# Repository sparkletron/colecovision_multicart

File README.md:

# Colecovision Multicart
## 15 in 1 flash ROM cart for Colecovision 32KiB ROMS.

author: Jay Convertino  

date: 2024.10.26

license: MIT

## Release Versions
### Current

  - pre-alpha

### Past

  - none
  
## Requirements

  - KiCad v7.X
  - xc8 v2.31 or greater
  - sdcc v4.0.0 or greater
  - make (build-essential)

  Tested on Ubuntu 22.04

## Brief Information

  Be sure to pull ALL submodules. The command for this is...

  ```console
  git submodule update --init --recursive
  ```

  This project creates a complete 15 in 1 multicart for the Colecovision. It will generate the needed ROM
  image, and firmware. Provides all the files needed for PCB creation, and the 3D printed case creation.

  No valid Colecovision ROMs are included in this project. Only valid ROM is the multicart application
  generated by RODAC. Game ROMs in RODAC are random data written in various bank sizes for testing only.

  Each folder in this root directory contains a part of the project, they are as follows.
  - docs, all documentation and detailed user manual.
  - schematic, Electrical schematic and gerbers from KiCAD.
  - src, all source files used to build the Multicart launcher and PIC support chip firmware.
  - models, STL files for printing out cart shell.

## Detailed Information

  For detailed usage information, please navigate to one of the following sources. They are the same, just in a different format.

  - [colecovision_multicart.pdf](docs/manual/colecovision_multicart.pdf)
  - [github wiki](https://github.com/sparkletron/colecovision_multicart/wiki)

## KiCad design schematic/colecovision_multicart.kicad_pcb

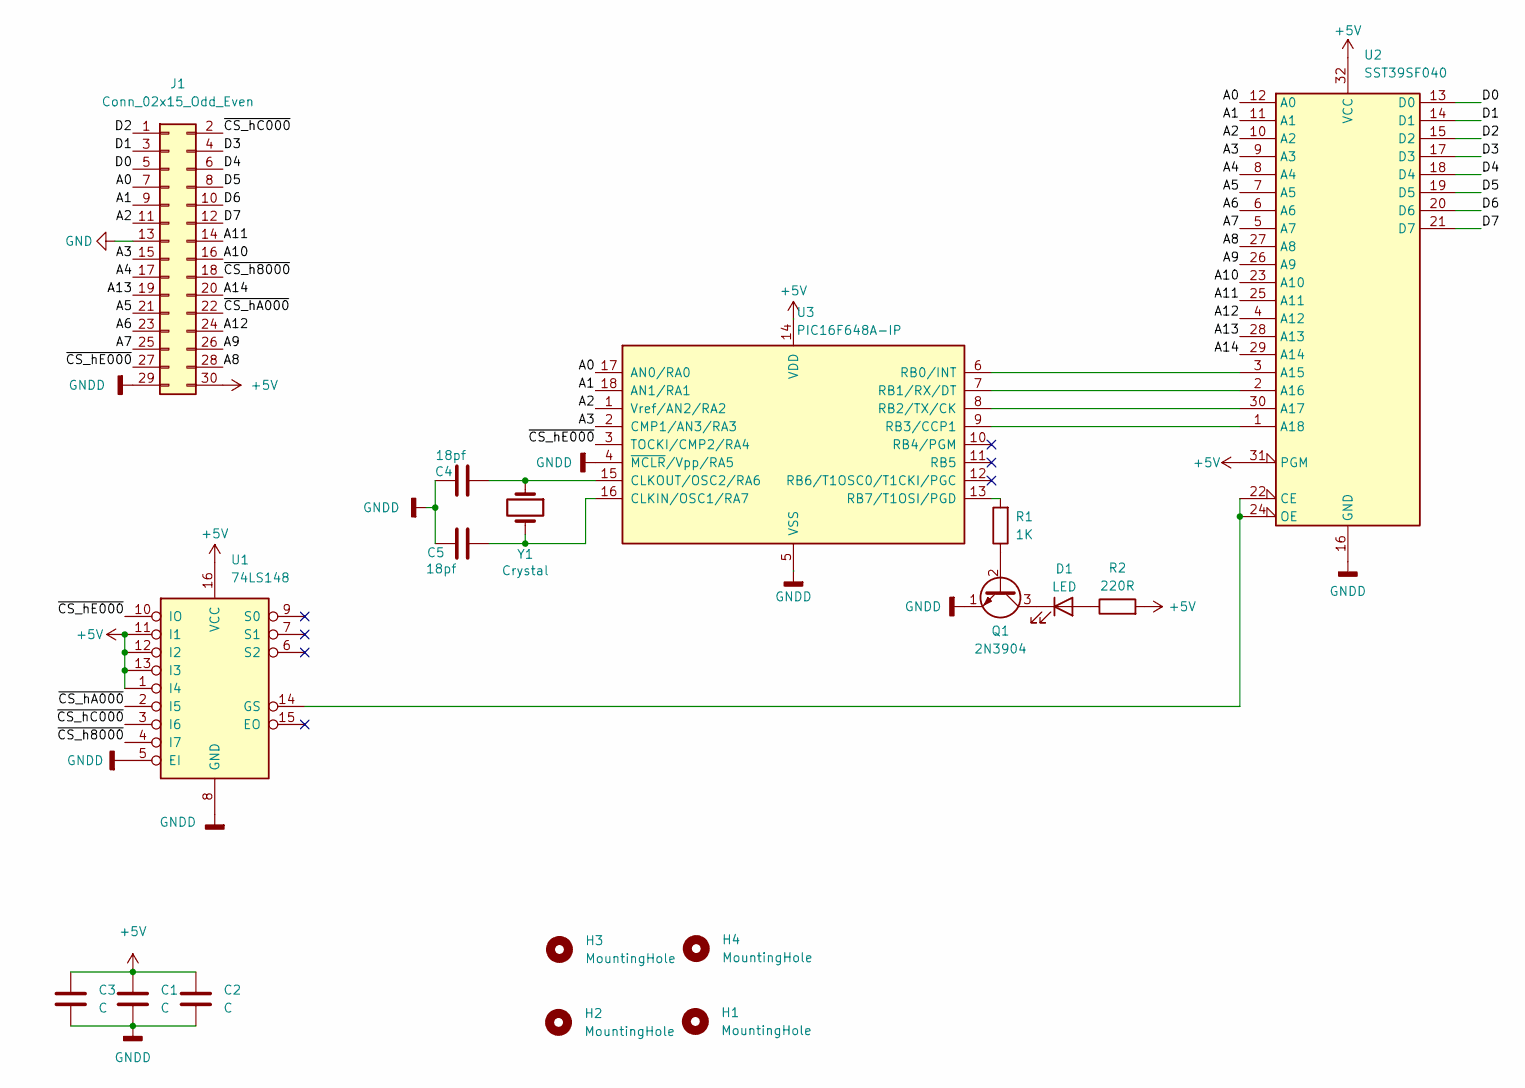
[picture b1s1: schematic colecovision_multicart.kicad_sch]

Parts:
C1, C2, C3: C; C_Disc_D5.0mm_W2.5mm_P5.00mm
C4, C5: 18pf; C_Disc_D3.0mm_W1.6mm_P2.50mm
D1: LED; LED_D3.0mm
H1, H2, H3, H4: MountingHole; MountingHole_3.2mm_M3_Pad
J1: Conn_02x15_Odd_Even; Colecovision_Cartridge
Q1: 2N3904; TO-92_Wide
R1: 1K; R_Axial_DIN0207_L6.3mm_D2.5mm_P7.62mm_Horizontal
R2: 220R; R_Axial_DIN0207_L6.3mm_D2.5mm_P7.62mm_Horizontal
U1: 74LS148; DIP-16_W7.62mm
U2: SST39SF040; DIP-32_W15.24mm
U3: PIC16F648A-IP; DIP-18_W7.62mm
Y1: Crystal; Crystal_HC49-4H_Vertical

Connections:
+5V: C1.1, C2.1, C3.1, J1.30, R2.2, U1.1 (I4), U1.11 (I1), U1.12 (I2), U1.13 (I3), U1.16 (VCC), U2.31 (PGM), U2.32 (VCC), U3.14 (VDD)
/A0: J1.7, U2.12 (A0), U3.17 (AN0/RA0)
/A1: J1.9, U2.11 (A1), U3.18 (AN1/RA1)
/A2: J1.11, U2.10 (A2), U3.1 (Vref/AN2/RA2)
/A3: J1.15, U2.9 (A3), U3.2 (CMP1/AN3/RA3)
/A4: J1.17, U2.8 (A4)
/A5: J1.21, U2.7 (A5)
/A6: J1.23, U2.6 (A6)
/A7: J1.25, U2.5 (A7)
/A8: J1.28, U2.27 (A8)
/A9: J1.26, U2.26 (A9)
/A10: J1.16, U2.23 (A10)
/A11: J1.14, U2.25 (A11)
/A12: J1.24, U2.4 (A12)
/A13: J1.19, U2.28 (A13)
/A14: J1.20, U2.29 (A14)
/D0: J1.5, U2.13 (D0)
/D1: J1.3, U2.14 (D1)
/D2: J1.1, U2.15 (D2)
/D3: J1.4, U2.17 (D3)
/D4: J1.6, U2.18 (D4)
/D5: J1.8, U2.19 (D5)
/D6: J1.10, U2.20 (D6)
/D7: J1.12, U2.21 (D7)
/~CS_h8000: J1.18, U1.4 (I7)
/~CS_hA000: J1.22, U1.2 (I5)
/~CS_hC000: J1.2, U1.3 (I6)
/~CS_hE000: J1.27, U1.10 (IO), U3.3 (TOCKI/CMP2/RA4)
GND: J1.13
GNDD: C1.2, C2.2, C3.2, C4.1, C5.2, J1.29, Q1.1 (E), U1.5 (EI), U1.8 (GND), U2.16 (GND), U3.4 (~MCLR/Vpp/RA5), U3.5 (VSS)
unnamed: D1.2 (A), R2.1
unnamed: D1.1 (K), Q1.3 (C)
unnamed: Q1.2 (B), R1.1
unnamed: U1.14 (GS), U2.22 (CE), U2.24 (OE)
unnamed: U2.3 (A15), U3.6 (RB0/INT)
unnamed: U2.2 (A16), U3.7 (RB1/RX/DT)
unnamed: U2.30 (A17), U3.8 (RB2/TX/CK)
unnamed: U2.1 (A18), U3.9 (RB3/CCP1)
unnamed: C5.1, U3.16 (CLKIN/OSC1/RA7), Y1.2
unnamed: C4.2, U3.15 (CLKOUT/OSC2/RA6), Y1.1
unnamed: R1.2, U3.13 (RB7/T1OSI/PGD)

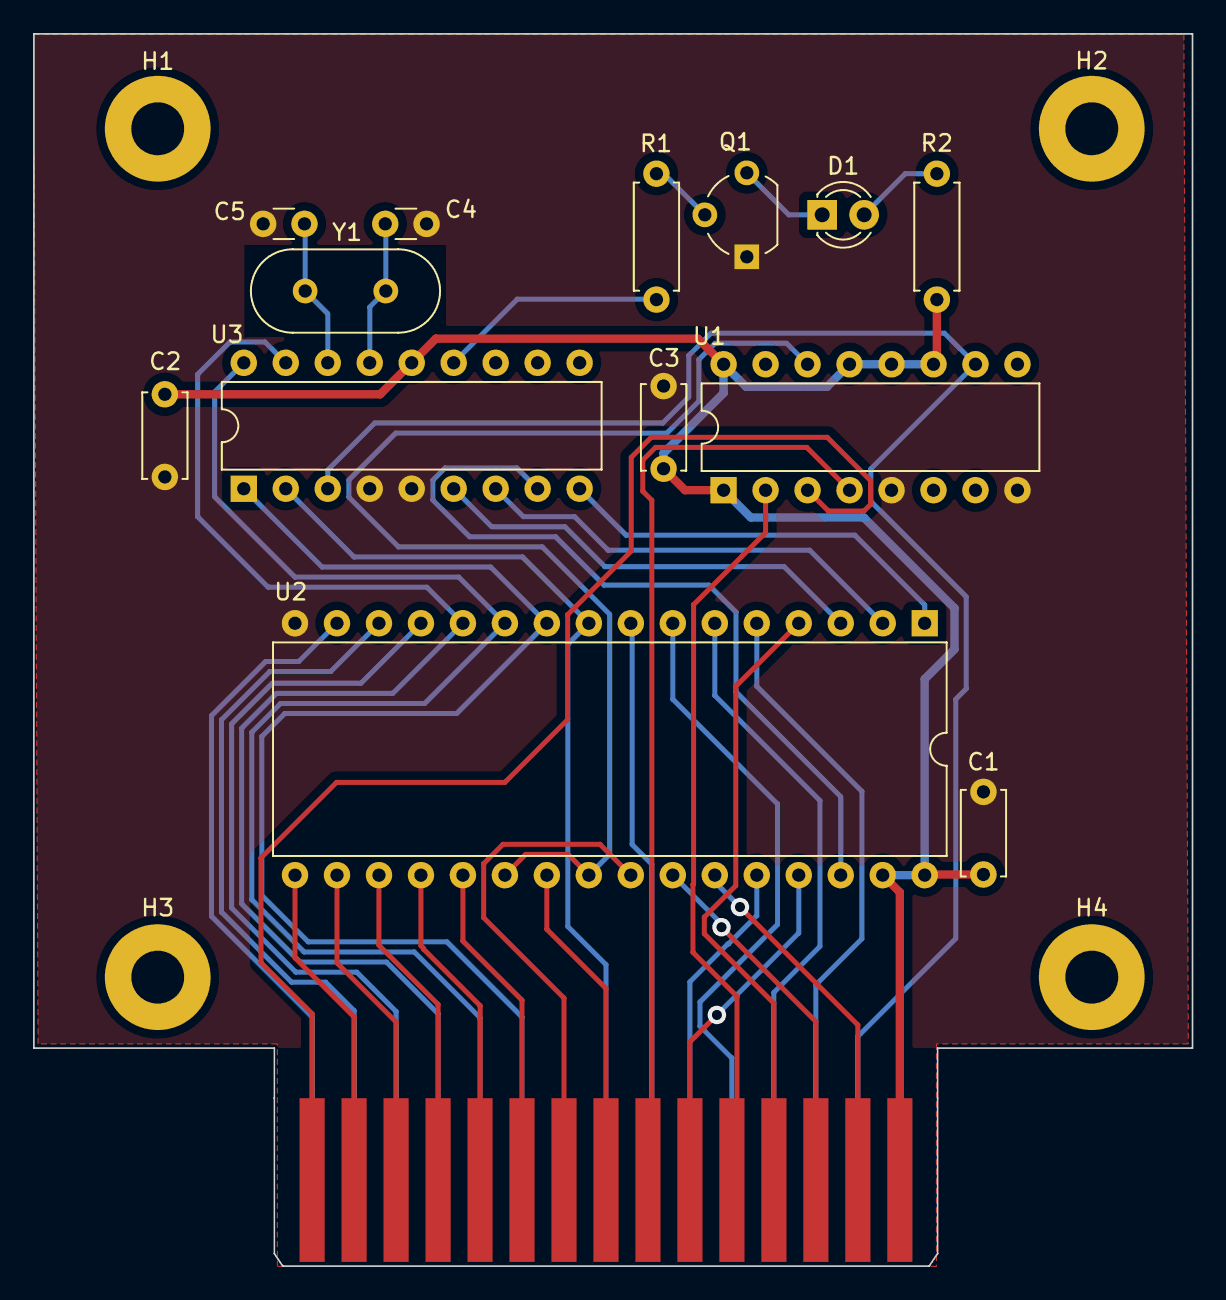
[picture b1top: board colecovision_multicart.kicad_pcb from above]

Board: 2 copper layers, 70.1 x 74.6 mm, 18 parts (0 on the bottom side), 40 nets.

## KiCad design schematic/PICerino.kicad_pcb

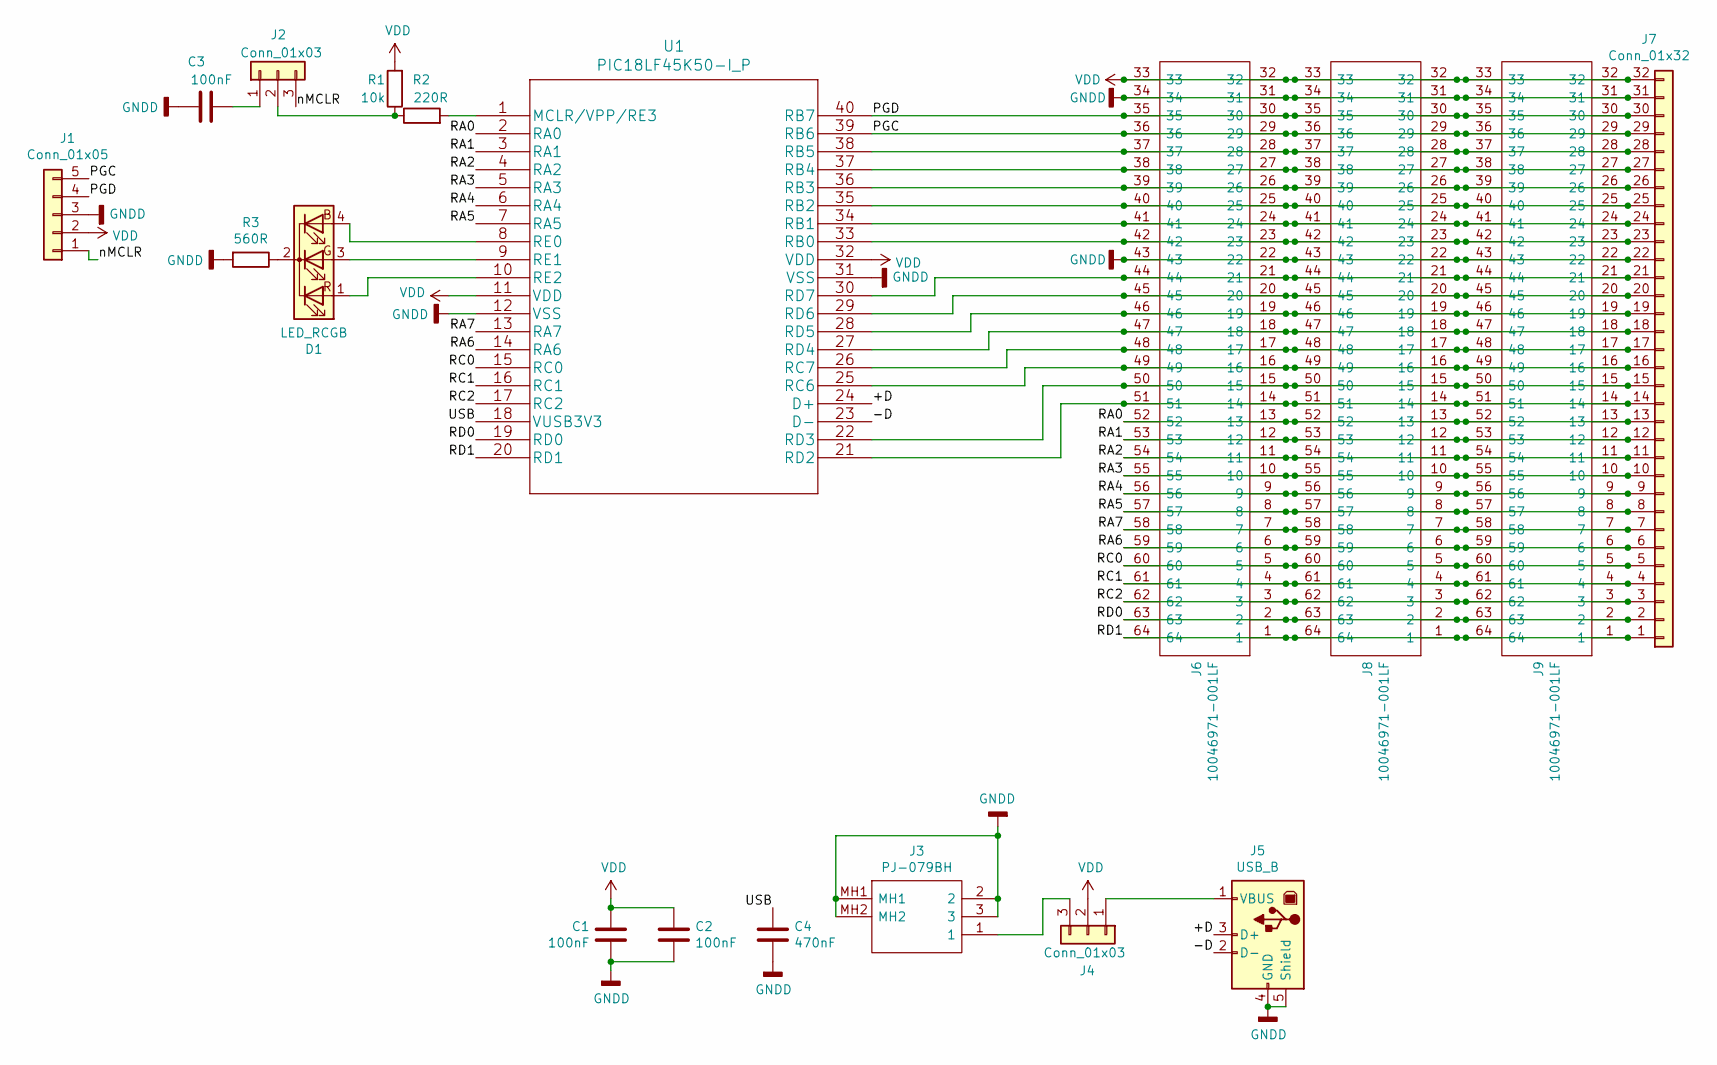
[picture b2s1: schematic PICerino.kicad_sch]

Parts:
C1, C2, C3: 100nF; C_Disc_D5.0mm_W2.5mm_P5.00mm
C4: 470nF; C_Disc_D5.0mm_W2.5mm_P5.00mm
D1: LED_RCGB; LED_D5.0mm-4_RGB_Wide_Pins
J1: Conn_01x05; PinHeader_1x05_P2.54mm_Vertical
J2, J4: Conn_01x03; PinHeader_1x03_P2.54mm_Vertical
J3: PJ-079BH; PJ079BH; Manufacturer_Part_Number PJ-079BH; Mouser Part Number 490-PJ-079BH
J5: USB_B; USB_B_OST_USB-B1HSxx_Horizontal
J6, J8, J9: 10046971-001LF; RHDR64W90P508X254_2X32_8786X929X1549P; Manufacturer_Part_Number 10046971-001LF; Mouser Part Number 649-10046971-001LF
J7: Conn_01x32; PinHeader_1x32_P2.54mm_Vertical
R1: 10k; R_Axial_DIN0207_L6.3mm_D2.5mm_P7.62mm_Horizontal
R2: 220R; R_Axial_DIN0207_L6.3mm_D2.5mm_P7.62mm_Horizontal
R3: 560R; R_Axial_DIN0207_L6.3mm_D2.5mm_P7.62mm_Horizontal
U1: PIC18LF45K50-I_P; DIP-40_W15.24mm_LongPads

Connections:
/+D: J5.3 (D+), U1.24 (D+)
/-D: J5.2 (D-), U1.23 (D-)
/PGC: J1.5, J6.29, J6.36, J7.29, J8.29, J8.36, J9.29, J9.36, U1.39 (RB6)
/PGD: J1.4, J6.30, J6.35, J7.30, J8.30, J8.35, J9.30, J9.35, U1.40 (RB7)
/RA0: J6.13, J6.52, J7.13, J8.13, J8.52, J9.13, J9.52, U1.2 (RA0)
/RA1: J6.12, J6.53, J7.12, J8.12, J8.53, J9.12, J9.53, U1.3 (RA1)
/RA2: J6.11, J6.54, J7.11, J8.11, J8.54, J9.11, J9.54, U1.4 (RA2)
/RA3: J6.10, J6.55, J7.10, J8.10, J8.55, J9.10, J9.55, U1.5 (RA3)
/RA4: J6.9, J6.56, J7.9, J8.9, J8.56, J9.9, J9.56, U1.6 (RA4)
/RA5: J6.8, J6.57, J7.8, J8.8, J8.57, J9.8, J9.57, U1.7 (RA5)
/RA6: J6.6, J6.59, J7.6, J8.6, J8.59, J9.6, J9.59, U1.14 (RA6)
/RA7: J6.7, J6.58, J7.7, J8.7, J8.58, J9.7, J9.58, U1.13 (RA7)
/RC0: J6.5, J6.60, J7.5, J8.5, J8.60, J9.5, J9.60, U1.15 (RC0)
/RC1: J6.4, J6.61, J7.4, J8.4, J8.61, J9.4, J9.61, U1.16 (RC1)
/RC2: J6.3, J6.62, J7.3, J8.3, J8.62, J9.3, J9.62, U1.17 (RC2)
/RD0: J6.2, J6.63, J7.2, J8.2, J8.63, J9.2, J9.63, U1.19 (RD0)
/RD1: J6.1, J6.64, J7.1, J8.1, J8.64, J9.1, J9.64, U1.20 (RD1)
/USB: C4.1, U1.18 (VUSB3V3)
/nMCLR: J1.1, J2.3
GNDD: C1.2, C2.2, C3.1, C4.2, J1.3, J3.2, J3.3, J3.MH1, J3.MH2, J5.4 (GND), J5.5 (Shield), J6.22, J6.31, J6.34, J6.43, J7.22, J7.31, J8.22, J8.31, J8.34, J8.43, J9.22, J9.31, J9.34, J9.43, R3.2, U1.12 (VSS), U1.31 (VSS)
unnamed: C3.2, J2.1
unnamed: D1.1 (RA), U1.10 (RE2)
unnamed: D1.2 (K), R3.1
unnamed: D1.3 (GA), U1.9 (RE1)
unnamed: D1.4 (BA), U1.8 (RE0)
unnamed: J2.2, R1.1, R2.1
unnamed: J3.1, J4.3
unnamed: J4.1, J5.1 (VBUS)
unnamed: J6.14, J6.51, J7.14, J8.14, J8.51, J9.14, J9.51, U1.21 (RD2)
unnamed: J6.15, J6.50, J7.15, J8.15, J8.50, J9.15, J9.50, U1.22 (RD3)
unnamed: J6.16, J6.49, J7.16, J8.16, J8.49, J9.16, J9.49, U1.25 (RC6)
unnamed: J6.17, J6.48, J7.17, J8.17, J8.48, J9.17, J9.48, U1.26 (RC7)
unnamed: J6.18, J6.47, J7.18, J8.18, J8.47, J9.18, J9.47, U1.27 (RD4)
unnamed: J6.19, J6.46, J7.19, J8.19, J8.46, J9.19, J9.46, U1.28 (RD5)
unnamed: J6.20, J6.45, J7.20, J8.20, J8.45, J9.20, J9.45, U1.29 (RD6)
unnamed: J6.21, J6.44, J7.21, J8.21, J8.44, J9.21, J9.44, U1.30 (RD7)
unnamed: J6.23, J6.42, J7.23, J8.23, J8.42, J9.23, J9.42, U1.33 (RB0)
unnamed: J6.24, J6.41, J7.24, J8.24, J8.41, J9.24, J9.41, U1.34 (RB1)
unnamed: J6.25, J6.40, J7.25, J8.25, J8.40, J9.25, J9.40, U1.35 (RB2)
unnamed: J6.26, J6.39, J7.26, J8.26, J8.39, J9.26, J9.39, U1.36 (RB3)
unnamed: J6.27, J6.38, J7.27, J8.27, J8.38, J9.27, J9.38, U1.37 (RB4)
unnamed: J6.28, J6.37, J7.28, J8.28, J8.37, J9.28, J9.37, U1.38 (RB5)
unnamed: R2.2, U1.1 (MCLR/VPP/RE3)
VDD: C1.1, C2.1, J1.2, J4.2, J6.32, J6.33, J7.32, J8.32, J8.33, J9.32, J9.33, R1.2, U1.11 (VDD), U1.32 (VDD)

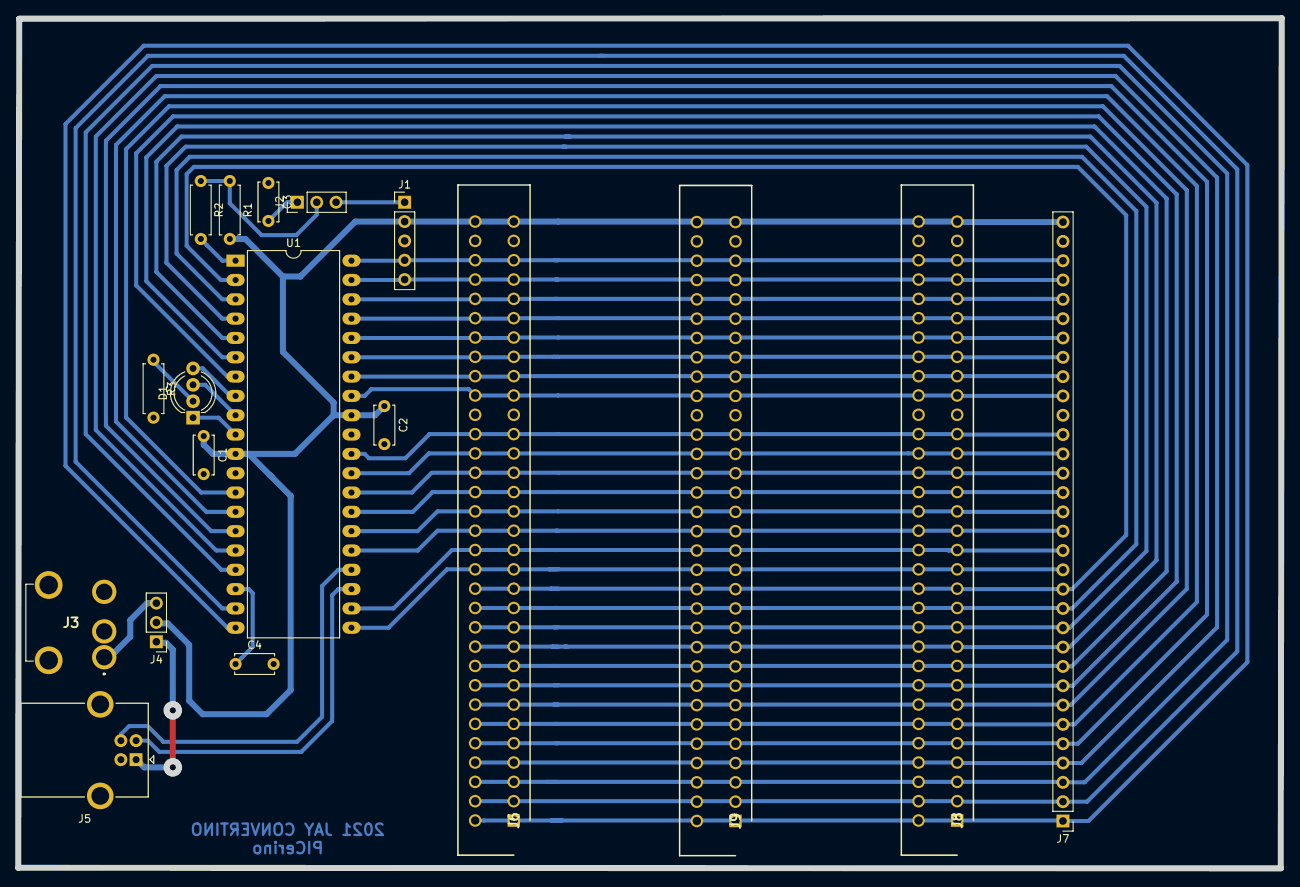
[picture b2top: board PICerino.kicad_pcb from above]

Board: 2 copper layers, 166.1 x 111.8 mm, 18 parts (0 on the bottom side), 44 nets.

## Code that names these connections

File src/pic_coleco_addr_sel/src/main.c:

/*******************************************************************************
 * @file    main.c
 * @author  Jay Convertino(electrobs@gmail.com)
 * @date    2024.10.16
 * @brief   Coleco Multicart Selection PIC uC
 *
 * CONTROLLER: PIC16F648A
 *
 * @license mit
 *
 * Copyright 2024 Johnathan Convertino
 *
 * Permission is hereby granted, free of charge, to any person obtaining a copy
 * of this software and associated documentation files (the "Software"), to deal
 * in the Software without restriction, including without limitation the rights
 * to use, copy, modify, merge, publish, distribute, sublicense, and/or sell
 * copies of the Software, and to permit persons to whom the Software is
 * furnished to do so, subject to the following conditions:
 *
 * The above copyright notice and this permission notice shall be included in
 * all copies or substantial portions of the Software.
 *
 * THE SOFTWARE IS PROVIDED "AS IS", WITHOUT WARRANTY OF ANY KIND, EXPRESS OR
 * IMPLIED, INCLUDING BUT NOT LIMITED TO THE WARRANTIES OF MERCHANTABILITY,
 * FITNESS FOR A PARTICULAR PURPOSE AND NONINFRINGEMENT. IN NO EVENT SHALL THE
 * AUTHORS OR COPYRIGHT HOLDERS BE LIABLE FOR ANY CLAIM, DAMAGES OR OTHER
 * LIABILITY, WHETHER IN AN ACTION OF CONTRACT, TORT OR OTHERWISE, ARISING
 * FROM, OUT OF OR IN CONNECTION WITH THE SOFTWARE OR THE USE OR OTHER DEALINGS
 * IN THE SOFTWARE.
 ******************************************************************************/

#include <xc.h>
#include <stdint.h>
#include <pic16f648a.h>

//setup to XTAL freq, for _delay macros
#define _XTAL_FREQ      20000000

// #pragma config statements should precede project file includes.
// Use project enums instead of #define for ON and OFF.

// CONFIG
#pragma config FOSC = HS        // Oscillator Selection bits (INTOSC oscillator: I/O function on RA6/OSC2/CLKOUT pin, I/O function on RA7/OSC1/CLKIN)
#pragma config WDTE = OFF       // Watchdog Timer Enable bit (WDT disabled)
#pragma config PWRTE = ON       // Power-up Timer Enable bit (PWRT enabled)
#pragma config MCLRE = OFF      // RA5/MCLR/VPP Pin Function Select bit (RA5/MCLR/VPP pin function is digital input, MCLR internally tied to VDD)
#pragma config BOREN = OFF      // Brown-out Detect Enable bit (BOD disabled)
#pragma config LVP = OFF        // Low-Voltage Programming Enable bit (RB4/PGM pin has digital I/O function, HV on MCLR must be used for programming)
#pragma config CPD = OFF        // Data EE Memory Code Protection bit (Data memory code protection off)
#pragma config CP = OFF         // Flash Program Memory Code Protection bit (Code protection off)

void main(void) 
{
    uint8_t stuff;
    //set each comparator for digital i/o on port a bits 0 to 3
    CMCONbits.CM0 = 1;
    CMCONbits.CM1 = 1;
    CMCONbits.CM2 = 1;
    
    //Port A set to all inputs.
    TRISA = 0xFF;
    
    //Port B set to outputs on all.
    TRISB = 0x00;
    
    //PORT B & A set to 0
    PORTB = 0;
    PORTA = 0;

    __delay_ms(1000);
    
    // 5 and 6 for bcf are bank select bits.  Clear them for bank 0.
    // STATUS 0 is the carry bit. check if the result of the add is a not a carry.
    // if its a not a carry lets store are work register to a general register at 0x20
    #asm
        bcf STATUS, 5
        bcf STATUS, 6
        test:
        movf  PORTA,w
        addlw 0xF0
        btfsc STATUS,0
        goto test
        movwf 0x20
    #endasm

    __delay_ms(1000);

    //get the data from general register 20, put it in are work register.
    //then move the work register to PORTB
    #asm
        movf 0x20,w
        movwf PORTB
    #endasm

    //you spin me right round like a record baby... FOREVER
    for(;;) {}
}

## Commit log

2022-01-31 cleaned up software readme
2022-02-13 fixed grammer
2022-04-30 expanded picerino to have 3 slots instead of 1. allowing multiple devices to be used.
2023-01-16 mit license update
2024-10-10 start change over to multi-cart
2024-10-26 added all updates to base repo
2024-10-26 major addition of everything, first working makefile for all build sources.
2024-10-27 add gerber files and wiki latex update
2024-10-27 update for git markdown
2024-10-27 update wiki
2024-10-27 update image name so markdown is created correctly
2024-10-27 added image
2024-10-27 added wiki to document source
2024-10-27 better update
2024-10-27 make brief less so
2024-10-27 update to make build processes easier
2024-10-27 format for easy copy
2024-10-27 add all datasheets for IC's
2024-10-27 update working to make diagram gen missing less confusing
2024-10-27 fix makefile phony, regen with fixed rodec name
2024-10-28 update links in detailed info
2024-11-01 updated documentation to first version that makes sense
2024-11-01 changed a word
2024-11-02 update RODAC to the newest push
2024-11-03 updated PIC readme, totally forgot about it
2024-12-02 fixed solder mask cart edge
